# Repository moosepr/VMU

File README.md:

# VMU
drop in pi board for Sega Dreamcast VMU

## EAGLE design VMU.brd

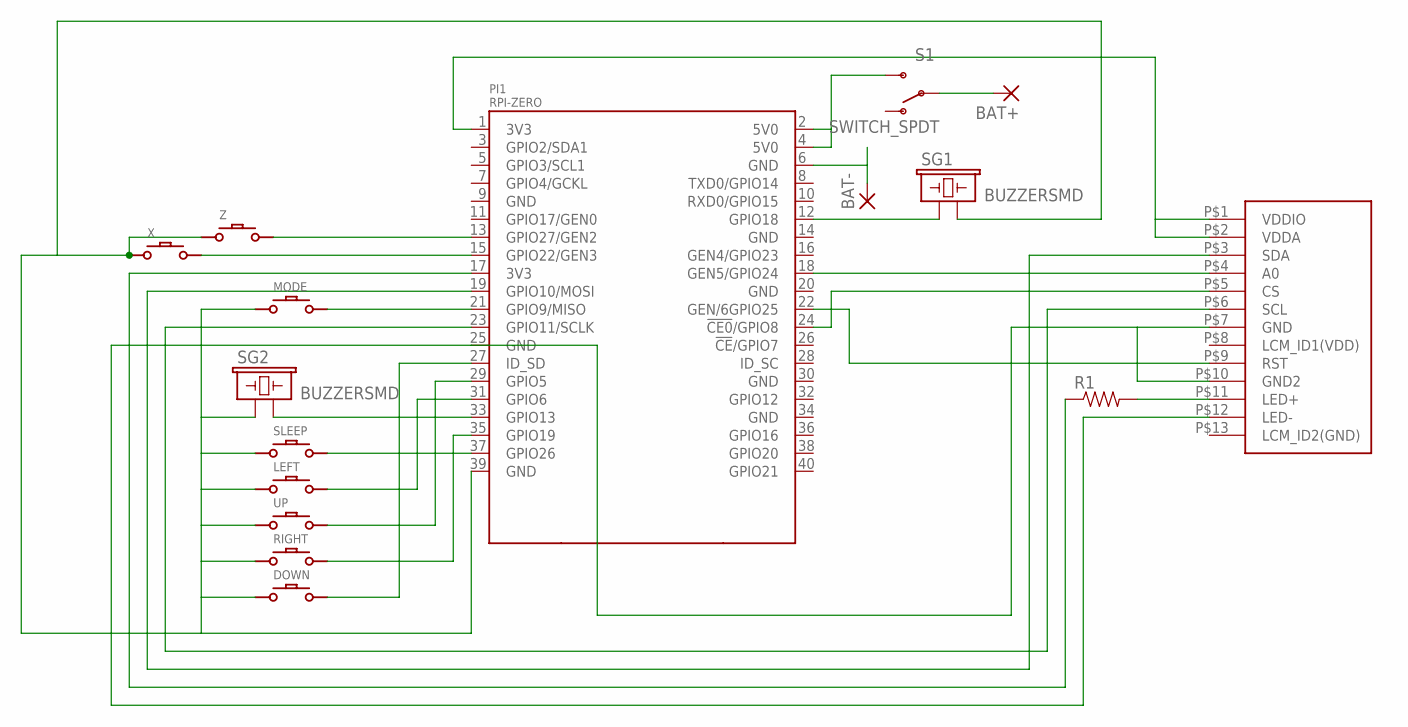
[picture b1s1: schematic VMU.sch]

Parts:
BAT+: SMD5; SMD2,54-5,08
BAT-: SMD5; SMD2,54-5,08
DOWN: DMG-BTNDS-BUTTON; DS-LITE-BTN
LEFT: DMG-BTNDS-BUTTON; DS-LITE-BTN
MODE: DMG-BTNDS-BUTTON; DS-LITE-BTN
PI1: RPI-ZERO; RASPBERRYPI_BASTELSTUBE_V13_RASPI_BOARD_B+_FULL
R1: RESISTOR0805-RES; 0805
RIGHT: DMG-BTNDS-BUTTON; DS-LITE-BTN
S1: SWITCH_SPDT; KPS-1290
SG1, SG2: BUZZERSMD; BUZZER-CMT1603
SLEEP: DMG-BTNDS-BUTTON; DS-LITE-BTN
U$1: ST7735S-1.44
UP: DMG-BTNDS-BUTTON; DS-LITE-BTN
X: DMG-BTNDS-BUTTON; DS-LITE-BTN
Z: DMG-BTNDS-BUTTON; DS-LITE-BTN

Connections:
3V3@1: PI1.1 (3V3), U$1.P$1 (VDDIO), U$1.P$2 (VDDA)
3V3@2: PI1.17 (3V3), R1.1
5V0@2: PI1.2 (5V0), PI1.4 (5V0), S1.S
GND@2: PI1.25 (GND), U$1.P$7 (GND), U$1.P$10 (GND2), U$1.P$12 (LED-)
GND@3: DOWN.P$3, LEFT.P$3, MODE.P$3, PI1.39 (GND), RIGHT.P$3, SG1.P$2 (2), SG2.P$1 (1), SLEEP.P$3, UP.P$3, X.P$3, Z.P$3
GND@8: BAT-.1, PI1.6 (GND)
unnamed: PI1.22 (GEN/6GPIO25), U$1.P$9 (RST)
unnamed: PI1.23 (GPIO11/SCLK), U$1.P$6 (SCL)
unnamed: PI1.19 (GPIO10/MOSI), U$1.P$3 (SDA)
unnamed: PI1.37 (GPIO26), SLEEP.P$4
unnamed: PI1.35 (GPIO19), RIGHT.P$4
unnamed: PI1.18 (GEN5/GPIO24), U$1.P$4 (A0)
unnamed: PI1.24 (!CE0!/GPIO8), U$1.P$5 (CS)
unnamed: LEFT.P$4, PI1.31 (GPIO6)
unnamed: PI1.29 (GPIO5), UP.P$4
unnamed: DOWN.P$4, PI1.27 (ID_SD)
unnamed: MODE.P$4, PI1.21 (GPIO9/MISO)
unnamed: PI1.13 (GPIO27/GEN2), Z.P$4
unnamed: PI1.12 (GPIO18), SG1.P$1 (1)
unnamed: R1.2, U$1.P$11 (LED+)
unnamed: PI1.33 (GPIO13), SG2.P$2 (2)
unnamed: PI1.15 (GPIO22/GEN3), X.P$4
unnamed: BAT+.1, S1.P

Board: 2 copper layers, 16 parts (1 on the bottom side), 23 nets, no tracks yet.

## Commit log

2017-09-02 Add files via upload
    initial test
2017-09-03 Add files via upload
    Some images of the board we are replacing. Credit to obsidianspider
2017-09-03 general outline

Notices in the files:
parts and their libraries:
SparkFun-Electromechanical: Licensing: Creative Commons ShareAlike 4.0 International - https://creativecommons.org/licenses/by-sa/4.0
